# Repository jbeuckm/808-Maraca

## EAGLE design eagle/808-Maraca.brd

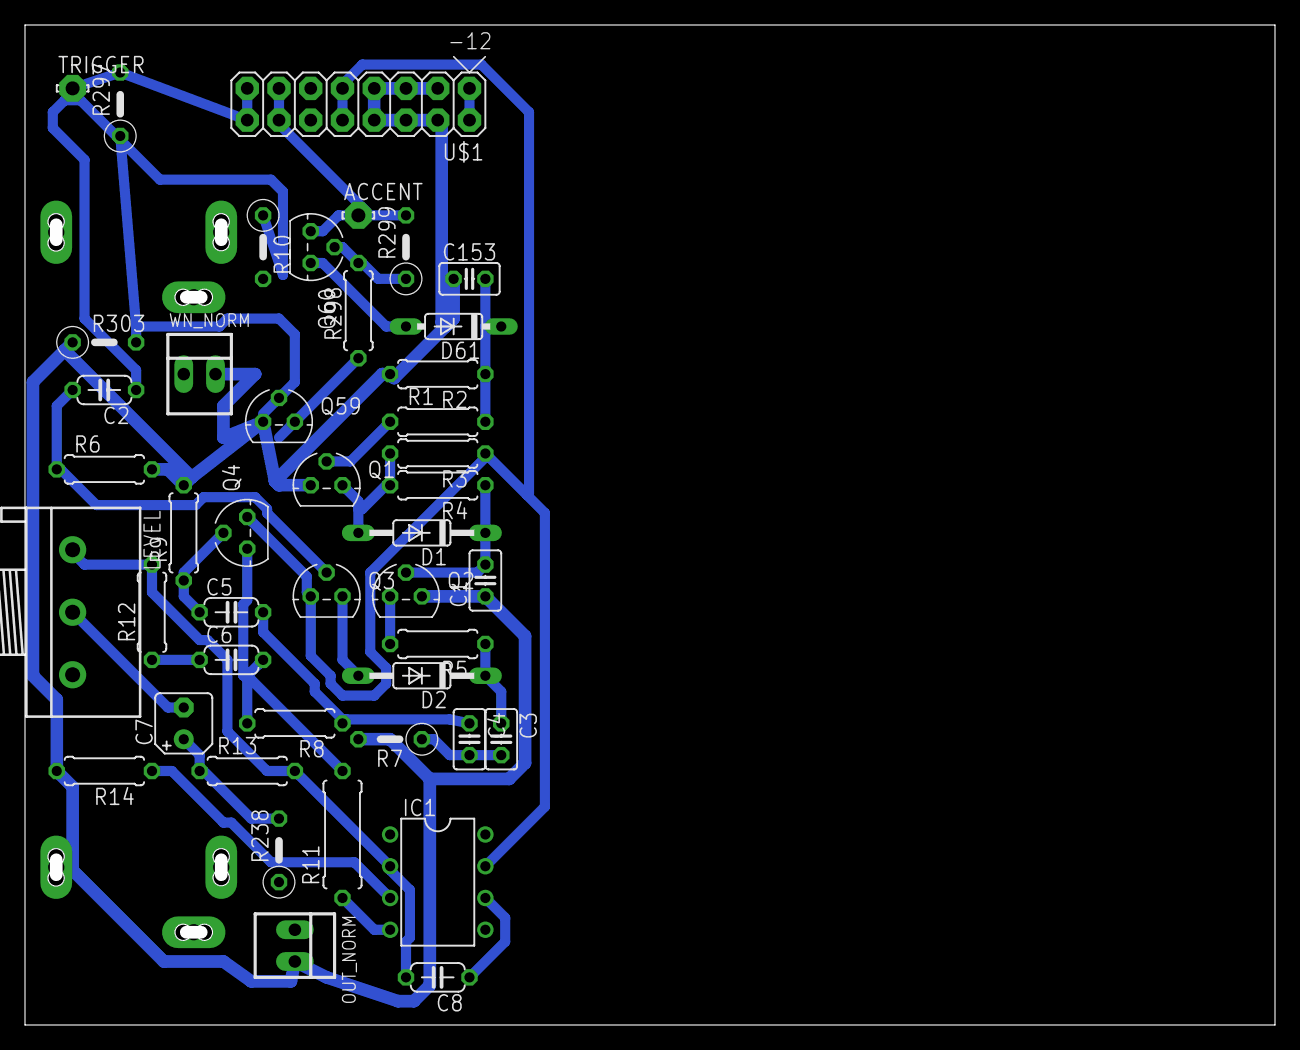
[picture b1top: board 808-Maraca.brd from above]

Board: 2 copper layers, 100.0 x 80.0 mm, 46 parts (0 on the bottom side), 31 nets.

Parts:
ACCENT: LSP11
C1: 33n; C025-025X050
C2: 47n; C050-024X044
C3: 10n; C025-025X050
C4: 1n; C025-025X050
C5: 1n; C050-024X044
C6: 10n; C050-024X044
C7: 33u; B45181A
C8: 220p; C050-024X044
C153: 100n; C025-025X050
D1, D2: 1N4148DO35-10; DO35-10
D61: 1N4148DO35-7; DO35-7
IC1: TL071P; DIL08
LEVEL: 100KA; 3RP/1610N
OUTPUT: AUDIO-JACK; ERTHENVAR-JACK-90DEG
OUT_NORM: 22-23-2021
Q1, Q4, Q59: 2N3904; TO92
Q2, Q3, Q60: 2N3906; TO92
R1: 220K; 0207/7
R2: 150K; 0207/7
R3, R12: 100K; 0207/7
R4, R13: 470K; 0207/7
R5, R298: 10K; 0207/7
R6: 1M; 0207/7
R7: 15K; 0207/5V
R8: 3k3; 0207/7
R9: 68k; 0207/7
R10: 6k8; 0207/5V
R11: 22K; 0309/10
R14: 47K; 0207/7
R238: 1K; 0207/5V
R297: 22K; 0207/5V
R299: 4K7; 0207/5V
R303: 10K; 0207/5V
TRIGGER: LSP11
U$1: POWER; POWER_16
WHITE_NOISE: AUDIO-JACK; ERTHENVAR-JACK-90DEG
WN_NORM: 22-23-2021

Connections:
+12V: IC1.7, Q3.3, Q4.1, R3.1, U$1.9, U$1.10
-12V: IC1.4, R11.1, U$1.1, U$1.2
GND: C1.1, C153.1, OUTPUT.P$1, OUT_NORM.2, Q1.3, Q2.1, Q59.3, R2.2, R6.2, R7.2, R9.2, R14.2, R303.1, U$1.3, U$1.4, U$1.5, U$1.6, U$1.7, U$1.8, WHITE_NOISE.P$1, WN_NORM.2
LT_LC_OUT: OUTPUT.P$3, R238.1
unnamed: Q60.2, R298.2, R299.1
unnamed: Q1.2, R1.1
unnamed: D1.A, Q1.1, R3.2, R4.2
unnamed: C1.2, D1.C, Q2.2, R4.1
unnamed: OUTPUT.P$2, OUT_NORM.1
unnamed: R10.2, WHITE_NOISE.P$3
unnamed: Q2.3, R5.2
unnamed: C7.+, C8.1, IC1.6, R13.1, R238.2
unnamed: C3.1, D2.C, R5.1
unnamed: D2.A, Q3.1
unnamed: C2.2, Q3.2, R6.1
unnamed: C3.2, C4.2, R7.1
unnamed: C4.1, C5.2, R8.1
unnamed: C2.1, R10.1
unnamed: C5.1, Q4.2, R9.1
unnamed: C6.2, Q4.3, R8.2, R11.2
unnamed: C8.2, IC1.2, LEVEL.1, R12.2, R13.2
unnamed: C6.1, R12.1
unnamed: C7.-, LEVEL.2
unnamed: R297.2, TRIGGER.MP, U$1.15, U$1.16
unnamed: WHITE_NOISE.P$2, WN_NORM.1
unnamed: IC1.3, R14.1
unnamed: Q59.2, R297.1, R303.2
unnamed: Q59.1, R298.1
unnamed: C153.2, D61.C, R1.2, R2.1
unnamed: D61.A, Q60.1
TRIG: ACCENT.MP, Q60.3, R299.2, U$1.13, U$1.14

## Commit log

2016-05-05 layout started
2016-05-05 routed badly
2016-05-06 tweaks
2016-05-06 well routed
2016-05-06 gcode
2016-05-07 routed with wn in jack
2016-05-07 cutout
